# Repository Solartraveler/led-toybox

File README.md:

# LED Spiel

## Idea

Add some RGB LEDs in a box with sound. Fun for kids.

## Features

- 5x5 RGB LEDs

- Mono sound output

- Up to 7 inputs for buttons

- Measure brightness of environment to adjust LED brigtness

- IR receiver allows every remote control to become an extra toy

- Runs with two rechargeable NIMH AAA batteries. Non rechargeable ones work too.

- Slow charge over USB (~80mA). Can be disabled for non rechargeable batteries.

- SD card for storing sound (mp3 files) and LED sequences

- SD card file exchange and firmware upload over USB

- The STM32F405 MCU is fast enough for mp3 decoding

- Costs for all parts is ~95€.

## Status

The PCB is soldered, the case is complete, the software for the toy works, but is incomplete.

Two push buttons are on the left side, if one is pressed during power up, the device enters DFU firmware download mode.

Four switches are there for selecting songs.

Some animations are available.

Missing featues:

- Data exchange over USB mass storage is slow

- The IR receiver is currently unused.

## History

Planning...

Soldering and debugging...

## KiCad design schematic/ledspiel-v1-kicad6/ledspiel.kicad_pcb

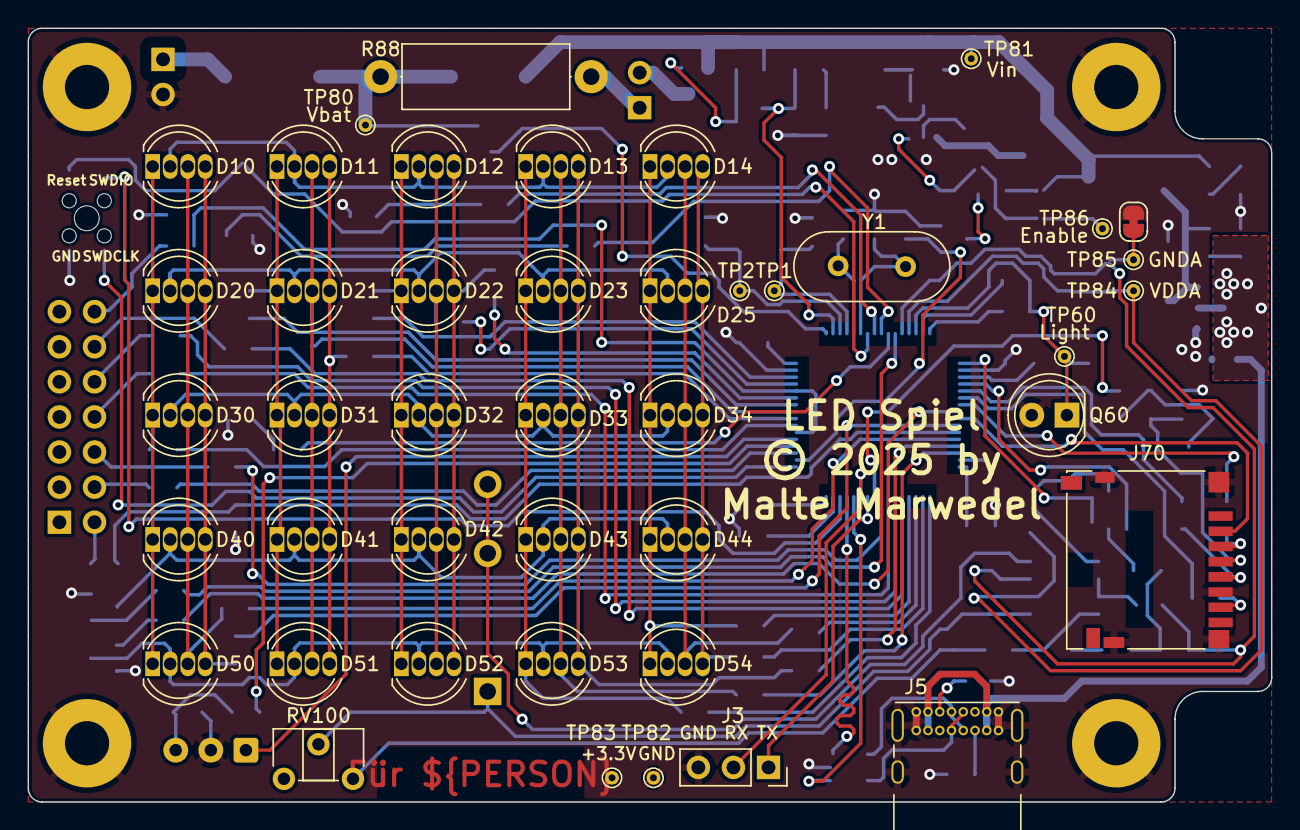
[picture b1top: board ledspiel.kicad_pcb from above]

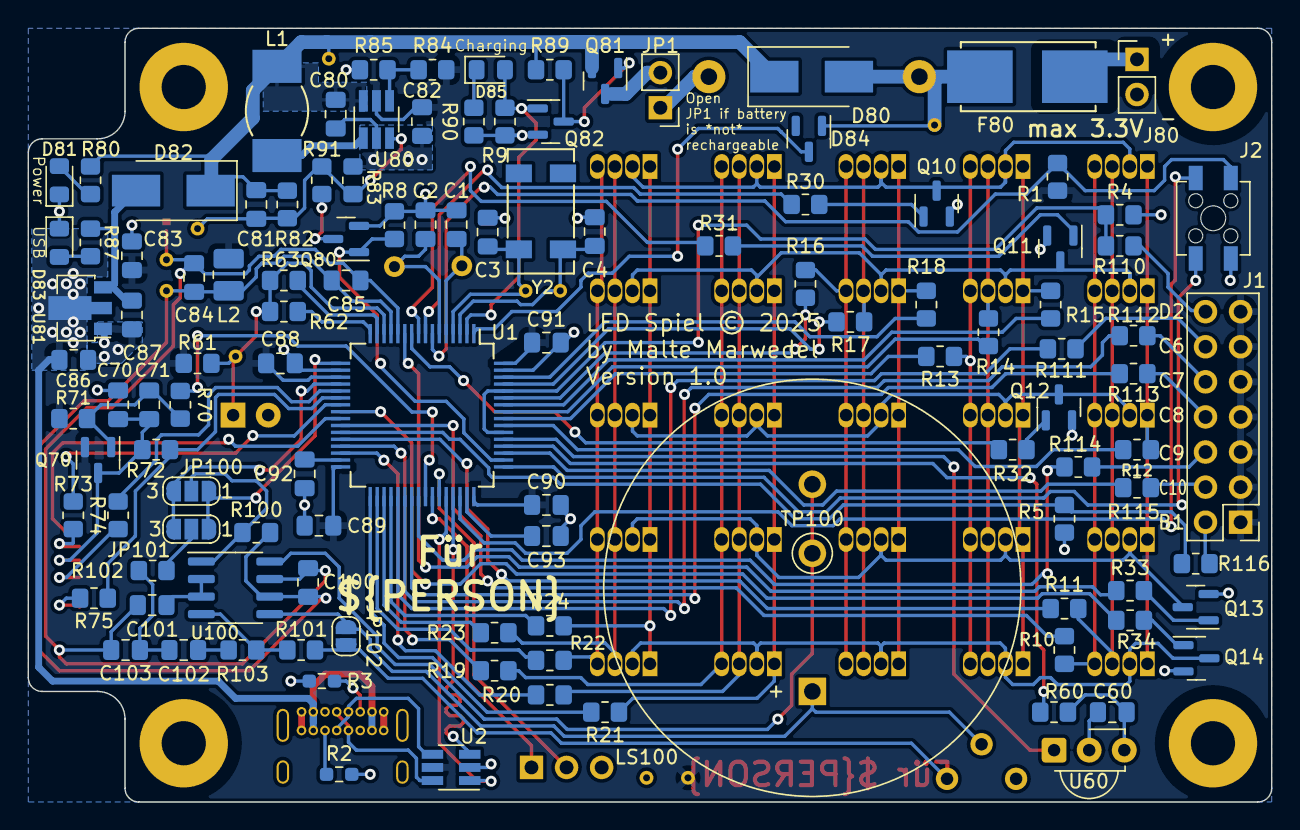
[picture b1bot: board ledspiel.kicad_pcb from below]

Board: 2 copper layers, 90.0 x 56.0 mm, 163 parts (116 on the bottom side), 125 nets.

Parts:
C1, C2, C71: 22pF; C_0805_2012Metric_Pad1.18x1.45mm_HandSolder
C3, C4: 10pF; C_0805_2012Metric_Pad1.18x1.45mm_HandSolder
C60, C70, C81, C86, C87, C92, C93, C101, C102: 2.2µF; C_0805_2012Metric_Pad1.18x1.45mm_HandSolder
C80, C82, C83, C84: 10µF; C_0805_2012Metric_Pad1.18x1.45mm_HandSolder
C85, C88, C89, C90, C91, C100: 100nF; C_0805_2012Metric_Pad1.18x1.45mm_HandSolder
C103: 18nF; C_0805_2012Metric_Pad1.18x1.45mm_HandSolder
D10, D11, D12, D13, D14, D20, D21, D22, D23, D25, D30, D31, D32, D33, D34, D40, D41, D42, D43, D44, D50, D51, D52, D53, D54: LED_RKBG; LED_D5.0mm-4_RGB
D80, D82: SK14; D_SMB_Handsoldering
D81, D83, D85: LED; LED_0805_2012Metric_Pad1.15x1.40mm_HandSolder
D84: BAT54C; SOT-23
F80: 250mA; SFM_OMNI-BLOK_Handsolder
H1, H2, H3, H4: MountingHole_Pad; MountingHole_3.2mm_M3_Pad
J1: Keys; PinHeader_2x07_P2.54mm_Vertical
J2: SWD Debug; Harwin_M20-7810245_2x02_P2.54mm_Vertical
J3: USART Debug; PinSocket_1x03_P2.54mm_Vertical
J5: USB_C_Receptacle_USB2.0; USB_C_Receptacle_GCT_USB4085
J70: Micro_SD_Card_Det; microSD_HC_Hirose_DM3D-SF
J80: Battery; PinHeader_1x02_P2.54mm_Vertical
JP1: Recharge; PinHeader_1x02_P2.54mm_Vertical
JP80: SolderJumper_2_Bridged; SolderJumper-2_P1.3mm_Bridged_RoundedPad1.0x1.5mm
JP100: AudioEnable; SolderJumper-3_P1.3mm_Open_RoundedPad1.0x1.5mm_NumberLabels
JP101: AudioData; SolderJumper-3_P1.3mm_Open_RoundedPad1.0x1.5mm_NumberLabels
JP102: SolderJumper_2_Open; SolderJumper-2_P1.3mm_Open_RoundedPad1.0x1.5mm
L1: 4.7µH; L_Fastron_PISG_Handsoldering
L2: 1µH; L_1008_2520Metric_Pad1.43x2.20mm_HandSolder
LS100: Speaker; Buzzer_D30mm_H11mm_P15mm
Q10, Q11, Q12, Q13, Q14, Q80, Q82: BSS138; SOT-23
Q60: SFH300-3/4; LED_D5.0mm_Clear
Q70, Q81: IRLML6402; SOT-23
R1, R80: 100kΩ; R_0805_2012Metric_Pad1.20x1.40mm_HandSolder
R2, R3: 5.1kΩ; R_0603_1608Metric_Pad0.98x0.95mm_HandSolder
R4, R5, R9, R71, R82, R83, R89, R100: 330kΩ; R_0805_2012Metric_Pad1.20x1.40mm_HandSolder
R8, R10, R13, R16, R19, R22, R87, R90, R101: 4.7kΩ; R_0805_2012Metric_Pad1.20x1.40mm_HandSolder
R11, R14, R17, R20, R23: 470Ω; R_0805_2012Metric_Pad1.20x1.40mm_HandSolder
R12, R15, R18, R21, R24: 560Ω; R_0805_2012Metric_Pad1.20x1.40mm_HandSolder
R30, R31, R32, R33, R34, R60, R70, R91, R102, R110, R111, R112, R113, R114, R115, R116: 220Ω; R_0805_2012Metric_Pad1.20x1.40mm_HandSolder
R61: 1MΩ; R_0805_2012Metric_Pad1.20x1.40mm_HandSolder
R62: 1kΩ; R_0805_2012Metric_Pad1.20x1.40mm_HandSolder
R63, R72, R103: 56kΩ; R_0805_2012Metric_Pad1.20x1.40mm_HandSolder
R73, R74, R75: 47Ω; R_0805_2012Metric_Pad1.20x1.40mm_HandSolder
R84: 470kΩ; R_0805_2012Metric_Pad1.20x1.40mm_HandSolder
R85: 270kΩ; R_0805_2012Metric_Pad1.20x1.40mm_HandSolder
R88: 12Ω; R_Axial_DIN0414_L11.9mm_D4.5mm_P15.24mm_Horizontal
RV100: 10kΩ; Potentiometer_Piher_PT-6-H_Horizontal
TP1, TP2, TP60, TP80, TP81, TP82, TP83, TP84, TP85, TP86: TestPoint; TestPoint_THTPad_D1.0mm_Drill0.5mm
TP100: TestPoint; TestPoint_THTPad_D2.0mm_Drill1.2mm
U1: STM32F405RGTx; LQFP-64_10x10mm_P0.5mm_Handsoldering
U2: USBLC6-2SC6; SOT-23-6_Handsoldering
U60: TSOP382xx; Vishay_MINICAST-3Pin
U80: MCP1640CH; SOT-23-6_Handsoldering
U81: MCP1703Ax-330xxMB; SOT-89-3
U100: LM4861; SOIC-8_3.9x4.9mm_P1.27mm
Y1: 8MHz; Crystal_HC49-U_Vertical
Y2: 32768Hz; Crystal_MP03

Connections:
+3.3V: C82.1, C83.1, C88.1, C89.1, C90.1, C91.1, J1.1, J1.3, J1.5, J1.7, J1.9, J1.11, J1.13, L2.1, Q70.2 (S), R1.2, R61.1, R71.2, R84.1, TP83.1, U1.19 (VDD), U1.32 (VDD), U1.48 (VDD), U1.64 (VDD), U2.5 (VBUS), U80.5 (VOUT)
/B10: R11.2, U1.28 (PB2)
/B10R: D10.3 (BA), D20.3 (BA), D30.3 (BA), D40.3 (BA), D50.3 (BA), R11.1
/B11: R14.2, U1.57 (PB5)
/B11R: D11.3 (BA), D21.3 (BA), D31.3 (BA), D41.3 (BA), D51.3 (BA), R14.1
/B12: R17.2, U1.61 (PB8)
/B12R: D12.3 (BA), D22.3 (BA), D32.3 (BA), D42.3 (BA), D52.3 (BA), R17.1
/B13: R20.2, U1.30 (PB11)
/B13R: D13.3 (BA), D23.3 (BA), D33.3 (BA), D43.3 (BA), D53.3 (BA), R20.1
/B14: R23.2, U1.35 (PB14)
/B14R: D14.3 (BA), D25.3 (BA), D34.3 (BA), D44.3 (BA), D54.3 (BA), R23.1
/BatUnprot: F80.1, J80.1
/Boot1: R5.1, R116.1, U1.27 (PB1)
/Charge: D85.2 (A), Q82.1 (G), R9.1, U1.2 (PC13)
/Dac1: JP100.3 (B), JP101.3 (B), U1.20 (PA4)
/G10: R10.2, U1.26 (PB0)
/G10R: D10.4 (GA), D20.4 (GA), D30.4 (GA), D40.4 (GA), D50.4 (GA), R10.1
/G11: R13.2, U1.56 (PB4)
/G11R: D11.4 (GA), D21.4 (GA), D31.4 (GA), D41.4 (GA), D51.4 (GA), R13.1
/G12: R16.2, U1.59 (PB7)
/G12R: D12.4 (GA), D22.4 (GA), D32.4 (GA), D42.4 (GA), D52.4 (GA), R16.1
/G13: R19.2, U1.29 (PB10)
/G13R: D13.4 (GA), D23.4 (GA), D33.4 (GA), D43.4 (GA), D53.4 (GA), R19.1
/G14: R22.2, U1.34 (PB13)
/G14R: D14.4 (GA), D25.4 (GA), D34.4 (GA), D44.4 (GA), D54.4 (GA), R22.1
/LightIn: Q60.1 (C), R61.2, R62.2, R63.2, TP60.1, U1.14 (PA0)
/LightOut1: R63.1, U1.15 (PA1)
/LightOut2: R62.1, U1.16 (PA2)
/Line1: R30.1, U1.8 (PC0)
/Line1Pwr: D10.2 (K), D11.2 (K), D12.2 (K), D13.2 (K), D14.2 (K), Q10.3 (D)
/Line2: R31.1, U1.9 (PC1)
/Line2Pwr: D20.2 (K), D21.2 (K), D22.2 (K), D23.2 (K), D25.2 (K), Q11.3 (D)
/Line3: R32.1, U1.10 (PC2)
/Line3Pwr: D30.2 (K), D31.2 (K), D32.2 (K), D33.2 (K), D34.2 (K), Q12.3 (D)
/Line4: R33.1, U1.11 (PC3)
/Line4Pwr: D40.2 (K), D41.2 (K), D42.2 (K), D43.2 (K), D44.2 (K), Q13.3 (D)
/Line5: R34.1, U1.24 (PC4)
/Line5Pwr: D50.2 (K), D51.2 (K), D52.2 (K), D53.2 (K), D54.2 (K), Q14.3 (D)
/PowerOff: Q80.1 (G), R8.2, U1.50 (PA15)
/R10: R12.2, U1.55 (PB3)
/R10R: D10.1 (RA), D20.1 (RA), D30.1 (RA), D40.1 (RA), D50.1 (RA), R12.1
/R11: R15.2, U1.58 (PB6)
/R11R: D11.1 (RA), D21.1 (RA), D31.1 (RA), D41.1 (RA), D51.1 (RA), R15.1
/R12: R18.2, U1.62 (PB9)
/R12R: D12.1 (RA), D22.1 (RA), D32.1 (RA), D42.1 (RA), D52.1 (RA), R18.1
/R13: R21.2, U1.33 (PB12)
/R13R: D13.1 (RA), D23.1 (RA), D33.1 (RA), D43.1 (RA), D53.1 (RA), R21.1
/R14: R24.2, U1.36 (PB15)
/R14R: D14.1 (RA), D25.1 (RA), D34.1 (RA), D44.1 (RA), D54.1 (RA), R24.1
/SdCs: J70.2 (DAT3/CD), U1.25 (PC5)
/SdOn: R70.1, U1.41 (PA8)
/Spi1Miso: R72.1, R75.1, U1.22 (PA6)
/Spi1Mosi: R73.1, U1.23 (PA7)
/Spi1Sck: R74.1, U1.21 (PA5)
/Swdclk: J2.1, U1.49 (PA14)
/Swdio: J2.3, U1.46 (PA13)
/Tim2Ch4: JP100.1 (A), JP101.1 (A), U1.17 (PA3)
/Usart1BootRx: J3.2, U1.43 (PA10)
/Usart1BootTx: J3.1, U1.42 (PA9)
/UsbDm: U1.44 (PA11), U2.1 (I/O1)
/UsbDp: U1.45 (PA12), U2.3 (I/O2)
/Vbat: D80.2 (A), D84.1, F80.2, R88.1, TP80.1
/Vbus: C86.1, J5.A4 (VBUS), J5.A9 (VBUS), J5.B4 (VBUS), J5.B9 (VBUS), U81.2 (VI)
/Vin: C80.1, C81.1, D80.1 (K), D82.1 (K), L1.1, Q81.2 (S), R80.1, R82.1, R89.1, TP81.1, U80.6 (VIN)
/nReset: J2.4, R1.1, U1.7 (NRST)
GND: C1.1, C2.1, C3.1, C4.1, C60.2, C70.2, C80.2, C82.2, C83.2, C86.2, C87.2, C88.2, C89.2, C90.2, C91.2, C92.2, C93.2, D81.1 (K), D83.1 (K), H1.1, H2.1, H3.1, H4.1, J2.2, J3.3, J5.A1 (GND), J5.A12 (GND), J5.B1 (GND), J5.B12 (GND), J5.S1 (SHIELD), J70.6 (VSS), J70.11 (SHIELD), J80.2, JP80.1 (A), Q10.2 (S), Q11.2 (S), Q12.2 (S), Q13.2 (S), Q14.2 (S), Q60.2 (E), Q80.2 (S), Q82.2 (S), R2.1, R3.1, R4.2, R5.2, R8.1, R9.2, R83.2, R85.2, R90.2, TP82.1, U1.18 (VSS), U1.63 (VSS), U2.2 (GND), U60.2 (GND), U80.2 (GND), U81.1 (GND)
GNDA: C84.2, C85.2, C100.2, C101.2, C103.2, JP80.2 (B), TP85.1, U1.12 (VSSA), U100.7 (GND)
unnamed: C1.2, U1.5 (PH0), Y1.2
unnamed: C2.2, U1.6 (PH1), Y1.1
unnamed: C3.2, TP1.1, U1.4 (PC15), Y2.1
unnamed: C4.2, TP2.1, U1.3 (PC14), Y2.2
unnamed: C60.1, R60.1, U60.3 (Vs)
unnamed: C70.1, C71.2, J70.4 (VDD), Q70.3 (D), R72.2
unnamed: C71.1, Q70.1 (G), R70.2, R71.1
unnamed: C81.2, R82.2, R83.1, R91.1, TP86.1, U80.3 (EN)
unnamed: C87.1, D82.2 (A), R87.1, U81.3 (VO)
unnamed: C92.1, U1.31 (VCAP_1)
unnamed: C93.1, U1.47 (VCAP_2)
unnamed: C101.1, U100.2 (BYPASS), U100.3 (IN+)
unnamed: C102.1, C103.1, R102.2
unnamed: C102.2, R103.1
unnamed: D81.2 (A), R80.2
unnamed: D83.2 (A), R87.2
unnamed: D84.3, U1.1 (VBAT)
unnamed: D85.1 (K), R90.1
unnamed: J1.2, R116.2
unnamed: J1.4, R115.2
unnamed: J1.6, R114.2
unnamed: J1.8, R113.2
unnamed: J1.10, R112.2
unnamed: J1.12, R111.2
unnamed: J1.14, R110.2
unnamed: J5.A5 (CC1), R3.2
unnamed: J5.A6 (D+), J5.B6 (D+), U2.4 (I/O2)
unnamed: J5.A7 (D-), J5.B7 (D-), U2.6 (I/O1)
unnamed: J5.B5 (CC2), R2.2
unnamed: J70.3 (CMD), R73.2
unnamed: J70.5 (CLK), R74.2
unnamed: J70.7 (DAT0), R75.2
unnamed: JP1.1 (A), R88.2
unnamed: JP1.2 (B), Q81.3 (D)
unnamed: JP100.2 (C), R100.1, U100.1 (SHDN)
unnamed: JP101.2 (C), R102.1
unnamed: JP102.1 (A), R101.1, RV100.3
unnamed: JP102.2 (B), LS100.1, RV100.2, U100.5 (Vo1)
unnamed: L1.2, U80.1 (SW)
unnamed: LS100.2, TP100.1, U100.8 (Vo2)
unnamed: Q10.1 (G), R30.2
unnamed: Q11.1 (G), R31.2
unnamed: Q12.1 (G), R32.2
unnamed: Q13.1 (G), R33.2
unnamed: Q14.1 (G), R34.2
unnamed: Q80.3 (D), R91.2
unnamed: Q81.1 (G), Q82.3 (D), R89.2
unnamed: R60.2, U1.52 (PC11)
unnamed: R84.2, R85.1, U80.4 (VFB)
unnamed: R101.2, R103.2, U100.4 (IN-)
unnamed: R4.1, R110.1, U1.54 (PD2), U1.60 (BOOT0)
unnamed: R111.1, U1.37 (PC6)
unnamed: R112.1, U1.38 (PC7)
unnamed: R113.1, U1.39 (PC8)
unnamed: R114.1, U1.40 (PC9)
unnamed: R115.1, U1.51 (PC10)
unnamed: U1.53 (PC12), U60.1 (OUT)
VDDA: C84.1, C85.1, C100.1, L2.2, R100.2, TP84.1, U1.13 (VDDA), U100.6 (VDD)

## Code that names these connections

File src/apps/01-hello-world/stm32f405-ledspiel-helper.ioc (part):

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Mcu.Name=STM32F405RGTx
Mcu.Package=LQFP64
Mcu.UserName=STM32F405RGTx
PA0-WKUP.GPIOParameters=GPIO_Label
PA0-WKUP.GPIO_Label=LightIn
PA0-WKUP.Signal=ADCx_IN0
PA1.GPIOParameters=GPIO_Label
PA1.GPIO_Label=LightOut1
PA1.Signal=GPIO_Output
PA10.Mode=Asynchronous
PA10.Signal=USART1_RX
PA11.Mode=Device_Only
PA11.Signal=USB_OTG_FS_DM
PA12.Mode=Device_Only
PA12.Signal=USB_OTG_FS_DP
PA13.Signal=SYS_JTMS-SWDIO
PA14.Signal=SYS_JTCK-SWCLK
PA15.GPIOParameters=GPIO_Label
PA15.GPIO_Label=PowerOff
PA15.Signal=GPIO_Output
PA2.GPIOParameters=GPIO_Label
PA2.GPIO_Label=LightOut2
PA2.Signal=GPIO_Output
PA3.GPIOParameters=GPIO_Label
PA3.GPIO_Label=AudioOn
PA3.Signal=GPIO_Output
PA4.GPIOParameters=GPIO_Label
PA4.GPIO_Label=Dac1
PA4.Signal=COMP_DAC1_group
PA5.Mode=Full_Duplex_Master
PA5.Signal=SPI1_SCK
PA6.Mode=Full_Duplex_Master
PA6.Signal=SPI1_MISO
PA7.Mode=Full_Duplex_Master
PA7.Signal=SPI1_MOSI
PA8.GPIOParameters=GPIO_Label
PA8.GPIO_Label=SdOn
PA8.Signal=GPIO_Output
PA9.Mode=Asynchronous
PA9.Signal=USART1_TX
PB0.GPIOParameters=GPIO_Label
PB0.GPIO_Label=G10
PB0.Signal=GPIO_Output
PB1.GPIOParameters=GPIO_Label
PB1.GPIO_Label=Boot1
PB1.Signal=GPIO_Input
PB10.GPIOParameters=GPIO_Label
PB10.GPIO_Label=G13
PB10.Signal=GPIO_Output
PB11.GPIOParameters=GPIO_Label
PB11.GPIO_Label=B13
PB11.Signal=GPIO_Output
PB12.GPIOParameters=GPIO_Label
PB12.GPIO_Label=R13
PB12.Signal=GPIO_Output
PB13.GPIOParameters=GPIO_Label
PB13.GPIO_Label=G14
PB13.Signal=GPIO_Output
PB14.GPIOParameters=GPIO_Label
PB14.GPIO_Label=B14
PB14.Signal=GPIO_Output
PB15.GPIOParameters=GPIO_Label
PB15.GPIO_Label=R14
PB15.Signal=GPIO_Output
PB2.GPIOParameters=GPIO_Label
PB2.GPIO_Label=B10
PB2.Signal=GPIO_Output
PB3.GPIOParameters=GPIO_Label
PB3.GPIO_Label=R10
PB3.Signal=GPIO_Output
PB4.GPIOParameters=GPIO_Label
PB4.GPIO_Label=G11
PB4.Signal=GPIO_Output
PB5.GPIOParameters=GPIO_Label
PB5.GPIO_Label=B11
PB5.Signal=GPIO_Output
PB6.GPIOParameters=GPIO_Label
PB6.GPIO_Label=R11
PB6.Signal=GPIO_Output
PB7.GPIOParameters=GPIO_Label
PB7.GPIO_Label=G12
PB7.Signal=GPIO_Output
PB8.GPIOParameters=GPIO_Label
PB8.GPIO_Label=B12
PB8.Signal=GPIO_Output
PB9.GPIOParameters=GPIO_Label
PB9.GPIO_Label=R12
PB9.Signal=GPIO_Output
PC0.GPIOParameters=GPIO_Label
PC0.GPIO_Label=Line1
PC0.Signal=GPIO_Output
PC1.GPIOParameters=GPIO_Label
PC1.GPIO_Label=Line2
PC1.Signal=GPIO_Output
PC10.GPIOParameters=GPIO_Label
PC10.GPIO_Label=Key6
PC10.Signal=GPIO_Input
PC11.GPIOParameters=GPIO_Label
PC11.GPIO_Label=RemoteOn
PC11.Signal=GPIO_Output
PC12.GPIOParameters=GPIO_Label
PC12.GPIO_Label=RemoteIn
PC12.Signal=GPIO_Input
PC13-ANTI_TAMP.GPIOParameters=GPIO_Label
PC13-ANTI_TAMP.GPIO_Label=Charge
PC13-ANTI_TAMP.Signal=GPIO_Output
PC14-OSC32_IN.Mode=LSE-External-Oscillator
PC14-OSC32_IN.Signal=RCC_OSC32_IN
PC15-OSC32_OUT.Mode=LSE-External-Oscillator
PC15-OSC32_OUT.Signal=RCC_OSC32_OUT
PC2.GPIOParameters=GPIO_Label
PC2.GPIO_Label=Line3
PC2.Signal=GPIO_Output
PC3.GPIOParameters=GPIO_Label
PC3.GPIO_Label=Line4
PC3.Signal=GPIO_Output
PC4.GPIOParameters=GPIO_Label
PC4.GPIO_Label=Line5
PC4.Signal=GPIO_Output
PC5.GPIOParameters=GPIO_Label
PC5.GPIO_Label=SdCs
PC5.Signal=GPIO_Output
PC6.GPIOParameters=GPIO_Label
PC6.GPIO_Label=Key2
PC6.Signal=GPIO_Input
PC7.GPIOParameters=GPIO_Label
PC7.GPIO_Label=Key3
PC7.Signal=GPIO_Input
PC8.GPIOParameters=GPIO_Label
PC8.GPIO_Label=Key4
PC8.Signal=GPIO_Input
PC9.GPIOParameters=GPIO_Label
PC9.GPIO_Label=Key5
PC9.Signal=GPIO_Input
PD2.GPIOParameters=GPIO_Label
PD2.GPIO_Label=Key1
PD2.Signal=GPIO_Input
PH0-OSC_IN.Mode=HSE-External-Oscillator
PH0-OSC_IN.Signal=RCC_OSC_IN
PH1-OSC_OUT.Mode=HSE-External-Oscillator
PH1-OSC_OUT.Signal=RCC_OSC_OUT
RCC.HSE_VALUE=8000000
RCC.SYSCLKFreq_VALUE=64000000
RCC.SYSCLKSource=RCC_SYSCLKSOURCE_PLLCLK
board=custom

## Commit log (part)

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2025-06-01 WIP: Schematic
2025-06-30 WIP schematic
    footprints for LEDs
2025-08-15 WIP: Foodprints mostly
2025-08-15 WIP: Schematic should be somehow complete
2025-08-17 WIP: Routing
2025-08-19 WIP PCB
2025-09-09 WIP: Routing complete
2025-09-14 WIP: Less warnings, less errors
2025-10-01 Might be complete
2025-10-13 WIP: Finished yet?
2025-10-14 Schematic: Add footprints
2025-10-14 Images: Add rendering, add project description
2025-10-17 WIP: Source code
2025-11-11 App: Hello World - test everything important
    Provides tests for:
    All LEDs
    All MCU pins
    SD card
    Measure brightness
    Measure battery voltage
2025-11-12 Schematic: Fix RGB LED footprints, fix power up, adjust LED resistor
    Fix the green and blue pins of the LEDs in the schematic to be switched.
    Fix R8 to be too high. Otherwise the power would immediately be switched off again.
    Decrease R87 to increase brightness of D83.
    Schematic version 1.1
2025-11-21 Common: Update linker scripts
    Add variant for running from RAM.
    Adjust heap and stack reqirements.
    Export symbol to adjust VTOR register by just changeing the linker script.
    This is required to load a program to a memory address unknown during compile time.
2025-11-21 Project: Add .gitignore
    No backup and build files please.
2025-11-21 ci: Add automated build on github
2025-12-13 App: hello-world: Add test for SWD debug connection
    Prints the input level. If it toggles while a debugger is connected, the wires work.
    Also allows setting back the pins for debug, as the pin test configures the pins to a mode
    where no debug connection is possible.
2025-12-13 Utilities: Add DFU upload script
    Supports both, uploading to internal bootloader by ST and
    to the RAM if the 02-loader firmware is running.
2025-12-13 Common: Add md5sum calculation from LwIP project
    Taken from version 2.1.3.
2025-12-13 Common: Add Lightweight USB Device Stack library
    This only adds the relevant source files for the STM32F405 from the libusb_stm32 project.
    A stm32_compat.h must be added to use the code.
    Taken from commit 396c2c50ad330b522104d0565525a7350e486fb9.
2025-12-13 Common: Algorithm: Add more common code
    Simple sprintf implementation
    Simple usage of JSMN parser
    Libc minimal size implementations
    TAR file reader
    They are just a copy from
    https://github.com/Solartraveler/UniversalboxArm/tree/a2017e5d17217898de555d77526e7ae967745359/src/common/algorithm
2025-12-13 Common: Add appInterface.h
    Shared file, will be used by main.c. This allows to have one common
    main.c for all projects.
2025-12-13 Common: Shared-init: Add files for using HAL with STM32F405 and the Ledspiel PCB
    Its a mix of CubeMX generated files with own modifications.
2025-12-13 img: Add a image of the PCB
    SWD and serial debug wires are connected.
2025-12-14 Common: ledspiellib: Add code for SPI, ADC and infrared
    Copied and adjusted from
    https://github.com/Solartraveler/UniversalboxArm/tree/a2017e5d17217898de555d77526e7ae967745359/src/apps/common/boxlib
    For the SPI and ADC, the code is based on the STM32F411 variant.
    The SPI DMA transfer has not been tested (yet).
2025-12-23 Apps: 01-hello-world: Fix setting pin for SD card
    The wrong chip select pin was configured. Worked even with the wrong value in place.
2025-12-23 Apps: 02-loader: Fix USB descriptor length
    Old value was suitable if there is an alternate config in place.
2025-12-23 Common: Ledspiellib: Add 144MHz option, fix setting prescaler, add function for reading µs timestamps
2025-12-23 WIP: Apps: Add 03-ledspiel
    This is the main firmware
2026-02-03 Shared-init: Fix linker warnings
    [...]/arm-none-eabi/lib/thumb/v7e-m+fp/hard/libc_nano.a(libc_a-closer.o): in function `_close_r':
    [...]/newlib/libc/reent/closer.c:47:(.text+0xc): warning: _close is not implemented and will always fail
    ... and more more warings like this.
    These were introduced by toolchaing arm-gnu-toolchain-11.3.rel1-x86_64-arm-none-eabi.
    So the warings are there when compiling with the libs provided by Debian 13 and were not there when using Debian 12.
2026-02-03 Common: libusb_stm32: Fix compiler warnings
    Backported from parts of the commit
    https://github.com/dmitrystu/libusb_stm32/commit/68d7e8c720703019412e8cd079a88a1145b4d5dc
2026-02-03 Apps: Add 03-ledspiel
    This is the main firmware.
    However currently the only functionality is reading the SD card over USB,
    and even this is really slow so wait for a long time until the USB drive appears in your OS.
    This is far from being finished.
2026-02-14 Algorithm: Improve SDMMC access
    With disabled CRC, its a lot faster.
2026-02-16 Apps: 01-hello-world: Fix audio test
    The audio test only generated a hearable output if DAC test was selected before.
2026-02-16 Common: Add fatfs lib for reading and writing files
    The code is taken from
    http://elm-chan.org/fsw/ff/00index_e.html version 0.14b.
    diskio.c has been adjusted to use the ledspiellib for reading from the flash (SD card).
2026-02-16 Algorithm: Add filesystem helper code
    The code is a reduced version from
    https://github.com/Solartraveler/UniversalboxArm/blob/119ab9479022e3513bfaef3f9c86a504cb2c153c/src/common/algorithm/filesystem.c
2026-02-18 02-loader: Add watchdog option, clean up code
    If a program specifies a watchdog option, this now enables the IWDG.
    This makes debugging progams which end in an endless loop much easier - no more power cycle needed.
    Also clean up some unused code. It was a leftover from the UniversalboxARM project.
2026-02-18 Common: Shared-init: Fix linker script for running from RAM with using the CCMRAM
    Without (NOLOAD) for .ccmram, as soon as this RAM is used by a variable,
    the generated .bin file would spawn the whole memory region, resulting in a 256MiB file.
    Obviously, this would not upload with the DFU loader.
2026-02-21 Common: Ledspiellib: Add timer32Bit
    A timer useful for simple performance measurements.
2026-02-21 Common: Ledspiellib: Add Stack sampler
    A simple way to figure out the maximum stack usage.
2026-03-08 Utilities: Add PixelAnimate
    This is a simple editor for generating sequences of animated pixels.
    The output format is uncompressed and supports 8 or 16 bit per color.
    The rendering takes place by supporting the following elements:
    Frame - a simple pixel frame
    Text - a scrolling text, supporting a 5x5 pixel font
    Roll - Roll the previous frame around
2026-03-08 Utilities: Add PixelXml2ani
    Console application which does the same conversion as the GUI program PixelAnimate can do.
    It just allows the usage from command line, so it is suitable for the use in a CI system.
2026-03-08 CI: Fix artifact path, switch Utilities and Apps build order
    The switch allows to use the utilities in the Apps build step.
2026-03-12 03-ledspiel: Add status messages and convert them to a header
    The files are currently not used.
2026-03-17 WIP LED matrix
    Shows an image, but a second call to Init does not show an image. Third call never returns.
2026-03-24 ledspiellib: Fix flash chip select
    If a hardware (ISR or DMA) is setting other pins on the GPIO, no read-modify-write is allowed by any other
    parts of the software as otherwise modifications of the hardware is overwritten to the previous state.
2026-03-24 ledspiellib: Add code for driving the LED matrix without any CPU load
    Shows an image by using only DMA and timer transfers.
2026-04-03 PixelAnimate: Add pause function to scene
    The previous rendered frame will increase its displayed time by the amount of pause.
    Useful to show the last frame of a text a little bit longer.
2026-04-03 Common: Move uninitialized variables from normal RAM to CCMRAM
    The CCMRAM is not used by the 02-loader project to store downloaded programs.
    Therefore its the best place to use it for uninitialized variables which are not used by any DMA.
    If initialized variables would be stored there, they would need to be copied at the startup, which
    would just take time and waste memory.
    Memory used by DMA is now declared with a keyword.
    This continues to allow the 03-ledspiel firmware to be loaded by the 02-loader project.
2026-04-03 common: algorithm: Change return value of FilesystemMount
    Having an uint8_t instead of a bool as return value allows to show a more useful
    error message. So the user knows why the mounting has failed.
2026-04-10 common: ledspiellib: Add code for reading key inputs
2026-04-10 02-loader: Fix failing to transfer 128KiB programs
    The stack was still at the end of the RAM and not in the CCMRAM.
    When a program with 128KiB was transferred, the stack was overwritten, resulting in a crash.
    127KiB worked.
2026-04-11 animations: Add the first 5 animations
    More to come.
2026-04-22 pixelAnimate: Add fade-in and fade-out operations
    Also fix the return values for the shift and rotate operations and getPixel functions.
2026-04-22 schematic: Update BOM
    Add the handle. This will protect the switches in the case of a drop.
2026-04-23 shared-init: Fix variables with the cached attribute were not zero initialized
    Variables which are zero initialized may not be placed in the .ccmram section, which
    is not initialized. The .bss section is in the .ccmram too, at least for the *.RAM.ld linker script.
2026-04-27 animations: Add 5 new animations
2026-05-03 ledspiellib: Adjust brightness of LED matrix without flickering
    This change allows to adjust the brighness without stopping the timers and DMA
    channels. As result no flicker is seen when changeing the brightness.
    The disadvantages are a higher refresh rate and therefore higher load on the
    memory bus. The load is always as high as it it was only on the lowest
    brightness before.
    Also the lowest brightness now switches the LED matrix off. So there
2026-05-03 ledspiellib: Add code for enabling and disabling the charger
    It is just a write to a GPIO pin.
2026-05-03 03-ledspiel: Support charging, fix keys
    Key input works as intended.
    Watchdog is stared by default.
    Temperature and voltages can be read.
    Charger starts if conditions are right.
    Matrix adjusts its brighness according to the surrounding brightness.
    Playback stops after 4 songs if no user input is present.
2026-05-12 03-ledspiel: Support auto power off, detect empty battery
    Also do not retry to charge after just 1s if an error is detected,
    in this case the waiting time is now 1min. In the case of an USB
    disconnect, the next charging is tried after 5s.
    It turns out there should have been another voltage measurement wire
    on the PCB to better detect if USB power is available.
    Now all minimal required featues for a useful toy are implemented.
2026-05-12 ledspiellib: Fix reading keys, support power down
    One key was setting two of the input bits. Also the bit order was
    not according to the documentation.
2026-05-18 animations: Add more files
    Charactes from 0...F. Useful to see which folder is actually selected.
2026-05-21 03-ledspiel: Decrease battery empty detection, enable USB or stop playback by keys
    An empty battery is now needs a measurement of 100mV less than before.
    Pressing the play key 2s now stops playing.
    Pressing the animation and play key for 2s now toggles the USB mode.
    If no mp3 is played, the CPU now is more often in the power saving mode.
    For sorting files qsort has been replaced by bubblesort, otherwise the program
    would not fit into the RAM anylonger.
2026-05-22 ledspiellib: Add pulldown to rs232 debug
    This fixes random char reception if no debug cable is connected.

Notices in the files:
schematic/ledspiel-v1-kicad6/ledspiel.kicad_pcb:
LED Spiel © 2025
© 2025 by
Malte Marwedel
